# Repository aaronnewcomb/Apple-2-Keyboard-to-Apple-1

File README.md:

# Apple-2-Keyboard-to-Apple-1

This is a simple PCB that converts the signals from an Apple II or Apple II+ keyboard to an Apple 1. There is a version that uses DIP-to-IDC connectors and another that uses DIP-to-DIP connectors. Pay close attention to the pinout when you make your connections! connecting the cables backwards can cause damage.

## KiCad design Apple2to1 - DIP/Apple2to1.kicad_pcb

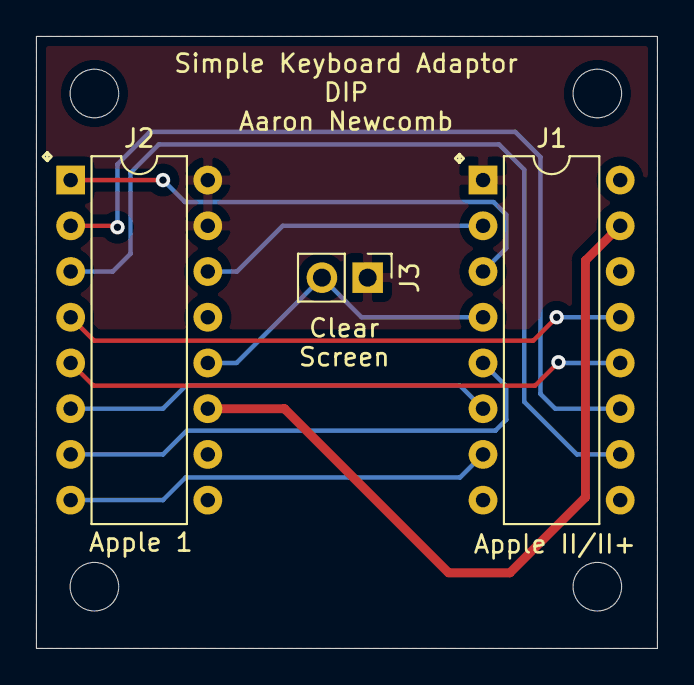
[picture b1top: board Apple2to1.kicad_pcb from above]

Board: 2 copper layers, 34.5 x 34.0 mm, 3 parts (0 on the bottom side), 13 nets.

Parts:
J1: Apple II/II+; DIP-16_W7.62mm
J2: Apple 1; DIP-16_W7.62mm
J3: Conn_01x02; PinHeader_1x02_P2.54mm_Vertical

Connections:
+5V: J1.1, J2.15, J2.16, J3.1
-12V: J1.15, J2.11
/data1: J1.12, J2.5
/data2: J1.13, J2.4
/data3: J1.10, J2.3
/data4: J1.11, J2.2
/data5: J1.6, J2.6
/data6: J1.5, J2.7
/data7: J1.7, J2.8
/reset: J1.3, J2.1
/strobe: J1.2, J2.14
GND: J1.8, J2.9
unnamed: J1.4, J2.12, J3.2
